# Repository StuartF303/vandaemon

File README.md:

# VanDaemon - Camper Van Control System

A comprehensive IoT control system for camper vans built with .NET 10 and Blazor WebAssembly. Monitor and control your van's systems including water tanks, LPG, lighting, heating, and more - all from your phone, tablet, or computer.

## Features

- **Real-time Monitoring**: Track water tanks, waste water, LPG, fuel, and battery levels in real-time
- **Interactive Controls**: Control lights, water pump, heater, and other systems with a touch-friendly interface
- **Configurable Alerts**: Get notified when tanks are running low or waste tanks are full
- **Multiple Van Types**: Support for different van models with customizable diagrams (default: Mercedes Sprinter LWB)
- **Modular Plugin System**: Easy integration with various hardware systems (Modbus, I2C, Victron Cerbo, etc.)
- **Web-Based Interface**: Access from any device with a web browser
- **Containerized Deployment**: Easy deployment with Docker on Raspberry Pi or other Linux systems
- **Offline-First**: Works without internet connectivity

## Quick Start

### Prerequisites

- [.NET 10.0 SDK](https://dotnet.microsoft.com/download/dotnet/10.0) (for development)
- [Docker](https://docs.docker.com/get-docker/) (for containerized deployment)
- Raspberry Pi 4 (2GB+ RAM recommended) or similar Linux system

### Running with Docker (Recommended)

1. Clone the repository:
```bash
git clone https://github.com/yourusername/vandaemon.git
cd vandaemon
```

2. Start the services:
```bash
docker compose up -d
```

For detailed Docker usage, configuration, and troubleshooting, see [DOCKER.md](DOCKER.md).

3. Access the web interface:
- Web UI: http://localhost:8080
- API: http://localhost:5000
- API Documentation: http://localhost:5000/swagger

### Running for Development

1. Build the solution:
```bash
./build.sh          # Linux/Mac
build.bat           # Windows
```

2. Run the API:
```bash
cd src/Backend/VanDaemon.Api
dotnet run
```

3. Run the Web UI (in a separate terminal):
```bash
cd src/Frontend/VanDaemon.Web
dotnet run
```

## Project Structure

```
VanDaemon/
├── src/
│   ├── Backend/
│   │   ├── VanDaemon.Api/              # REST API and SignalR hubs
│   │   ├── VanDaemon.Core/             # Domain models and interfaces
│   │   ├── VanDaemon.Application/      # Business logic services
│   │   ├── VanDaemon.Infrastructure/   # Data access and external services
│   │   └── VanDaemon.Plugins/          # Hardware integration plugins
│   │       ├── Abstractions/           # Plugin interfaces
│   │       ├── Simulated/              # Simulated hardware (for testing)
│   │       ├── Modbus/                 # Modbus integration
│   │       ├── I2C/                    # I2C sensor integration
│   │       └── Victron/                # Victron Cerbo integration
│   └── Frontend/
│       └── VanDaemon.Web/              # Blazor WebAssembly application
├── tests/                              # Unit and integration tests
├── docs/                               # Documentation
├── docker/                             # Docker configuration
└── .github/workflows/                  # CI/CD pipelines
```

## Architecture

VanDaemon follows a clean architecture pattern with clear separation of concerns:

- **Frontend**: Blazor WebAssembly with MudBlazor UI components
- **Backend API**: ASP.NET Core Web API with SignalR for real-time updates
- **Plugin System**: Modular hardware integration layer supporting multiple protocols
- **Data Storage**: JSON file storage for configuration, in-memory cache for real-time data

See [PROJECT_PLAN.md](PROJECT_PLAN.md) for detailed architecture documentation.

## Hardware Integration

VanDaemon supports multiple hardware integration methods through its plugin system:

### Supported Plugins

1. **Simulated Plugin** (Default) - For testing and development
2. **MqttLedDimmer Plugin** - VANDIMMER-4CH+2A LED dimmer boards over MQTT. Auto-discovers
   devices from their retained `config` message and registers each channel as a Dimmer
   control. Working against real hardware as of 2026-09-10; see
   [hw/VDDimmer/firmware/README.md](hw/VDDimmer/firmware/README.md) for the topic contract.
3. **Modbus Plugin** - For Modbus TCP/RTU devices
4. **I2C Plugin** - For direct I2C sensor integration
5. **Victron Plugin** - For Victron Cerbo GX integration via MQTT

Driving real hardware needs an MQTT broker the API can reach; `MqttLedDimmer:MqttBroker` in
`appsettings.json` defaults to `localhost:1883`.

### Adding a New Plugin

See [docs/deployment/plugin-development.md](docs/deployment/plugin-development.md) for instructions on creating custom hardware plugins.

## Configuration

### System Settings

Configure the system through the web interface Settings page or by editing the configuration files:

- `appsettings.json` - API configuration
- Environment variables - Runtime configuration

### Van Diagram Configuration

Customize the van diagram to match your vehicle:

1. Create an SVG diagram of your van (facing left)
2. Add the diagram to `src/Frontend/VanDaemon.Web/wwwroot/diagrams/`
3. Configure overlay positions in the Settings page

## Deployment

VanDaemon supports multiple deployment options:

### Cloud Deployment (Fly.io)

Deploy VanDaemon to the cloud for remote access as a single combined container:

```bash
# Install Fly.io CLI
curl -L https://fly.io/install.sh | sh

# Login and deploy
flyctl auth login
flyctl apps create vandaemon
flyctl deploy
```

Access your application at:
- **Single URL**: https://vandaemon.fly.dev
  - Web Frontend: `/`
  - API Backend: `/api`
  - SignalR WebSocket: `/hubs`
  - Health Check: `/health`

#### Architecture
The Fly.io deployment uses a single container with:
- **Nginx** (Port 8080) - Serves Blazor WASM static files and proxies API/WebSocket requests
- **.NET API** (Port 5000 internal) - Handles REST API and SignalR connections
- **Supervisor** - Manages both nginx and API processes

#### Key Features
- **Single Endpoint**: All services accessible from one URL
- **WebSocket Support**: Nginx configured for long-lived SignalR connections
- **Health Checks**: Automatic monitoring via `/health` endpoint
- **Auto-Scaling**: Machines stop when idle to save costs
- **GitHub Actions**: Automatic deployment on push to main branch

For detailed instructions including GitHub Actions auto-deployment, see **[DEPLOYMENT.md](DEPLOYMENT.md)**

### Local/Raspberry Pi Deployment

### Step 1: Prepare the Raspberry Pi

```bash
# Update system
sudo apt update && sudo apt upgrade -y

# Install Docker (includes Docker Compose V2)
curl -fsSL https://get.docker.com -o get-docker.sh
sudo sh get-docker.sh

# Add user to docker group
sudo usermod -aG docker $USER
```

### Step 2: Clone and Deploy

```bash
git clone https://github.com/yourusername/vandaemon.git
cd vandaemon
docker compose up -d
```

### Step 3: Configure Hardware Access

For GPIO/I2C access, you may need to:

```bash
# Enable I2C
sudo raspi-config
# Select: Interface Options -> I2C -> Enable

# Add user to i2c group
sudo usermod -aG i2c $USER
```

### Step 4: Set Up Auto-Start

```bash
# Create systemd service
sudo nano /etc/systemd/system/vandaemon.service
```

Add the following content:
```ini
[Unit]
Description=VanDaemon Control System
Requires=docker.service
After=docker.service

[Service]
Type=oneshot
RemainAfterExit=yes
WorkingDirectory=/home/pi/vandaemon
ExecStart=/usr/bin/docker compose up -d
ExecStop=/usr/bin/docker compose down

[Install]
WantedBy=multi-user.target
```

Enable and start:
```bash
sudo systemctl enable vandaemon
sudo systemctl start vandaemon
```

## API Documentation

The API is documented with OpenAPI/Swagger. Access the interactive documentation at:
- http://localhost:5000/swagger (when running locally)
- https://vandaemon.fly.dev/swagger (when deployed)

### Key Endpoints

- `GET /api/tanks` - Get all tanks
- `GET /api/tanks/{id}/level` - Get current tank level
- `POST /api/tanks/refresh` - Refresh all tank levels
- `PUT /api/tanks/{id}` - Update tank configuration
- `GET /health` - Health check endpoint (returns status and timestamp)

### Real-Time Updates

SignalR hub for real-time telemetry updates:
- **Local**: ws://localhost:5000/hubs/telemetry
- **Cloud**: wss://vandaemon.fly.dev/hubs/telemetry

The hub broadcasts tank levels, control states, and alerts to all connected clients.

## Development

### Building from Source

```bash
# Build solution
dotnet build VanDaemon.sln

# Run tests
dotnet test VanDaemon.sln

# Run specific project
cd src/Backend/VanDaemon.Api
dotnet run
```

### Running Tests

```bash
# Run all tests
dotnet test

# Run with coverage
dotnet test --collect:"XPlat Code Coverage"
```

## Roadmap

See [PROJECT_PLAN.md](PROJECT_PLAN.md) for the detailed development roadmap.

## Troubleshooting

### Common Issues

**Issue**: Cannot connect to API from web interface
- Check that API is running on http://localhost:5000
- Verify CORS settings in `appsettings.json`
- Check browser console for errors
- The frontend automatically uses the current host URL (no configuration needed)

**Issue**: Docker containers won't start
- Run `docker compose logs` to check logs
- Ensure ports 5000 and 8080 are not in use
- Verify Docker daemon is running

**Issue**: Sensors not reading values
- Check plugin configuration in Settings
- Verify hardware connections
- Check API logs for errors

**Issue**: SignalR WebSocket connections failing
- Verify health endpoint is accessible: `curl https://your-app.fly.dev/health`
- Check nginx logs for WebSocket upgrade errors
- Ensure nginx is configured with proper WebSocket headers
- Check for firewall blocking WebSocket connections (port 443 for wss://)

**Issue**: Fly.io deployment health checks failing
- Verify the `/health` endpoint returns 200 OK
- Check logs: `flyctl logs --app vandaemon`
- Ensure nginx and API are both running: `flyctl ssh console -C "supervisorctl status"`

**Issue**: Frontend making requests to localhost in production
- This is now fixed automatically - the frontend uses `builder.HostEnvironment.BaseAddress`
- In production, it will use the deployed URL (e.g., https://vandaemon.fly.dev)
- In development, it will use http://localhost:8080

## License

This project is licensed under the MIT License - see the [LICENSE](LICENSE) file for details.

## Acknowledgments

- [MudBlazor](https://mudblazor.com/) - Material Design components for Blazor
- [NModbus](https://github.com/NModbus/NModbus) - Modbus communication library
- [Victron Energy](https://www.victronenergy.com/) - For their excellent products and documentation

---

Built with ❤️ for the camper van community

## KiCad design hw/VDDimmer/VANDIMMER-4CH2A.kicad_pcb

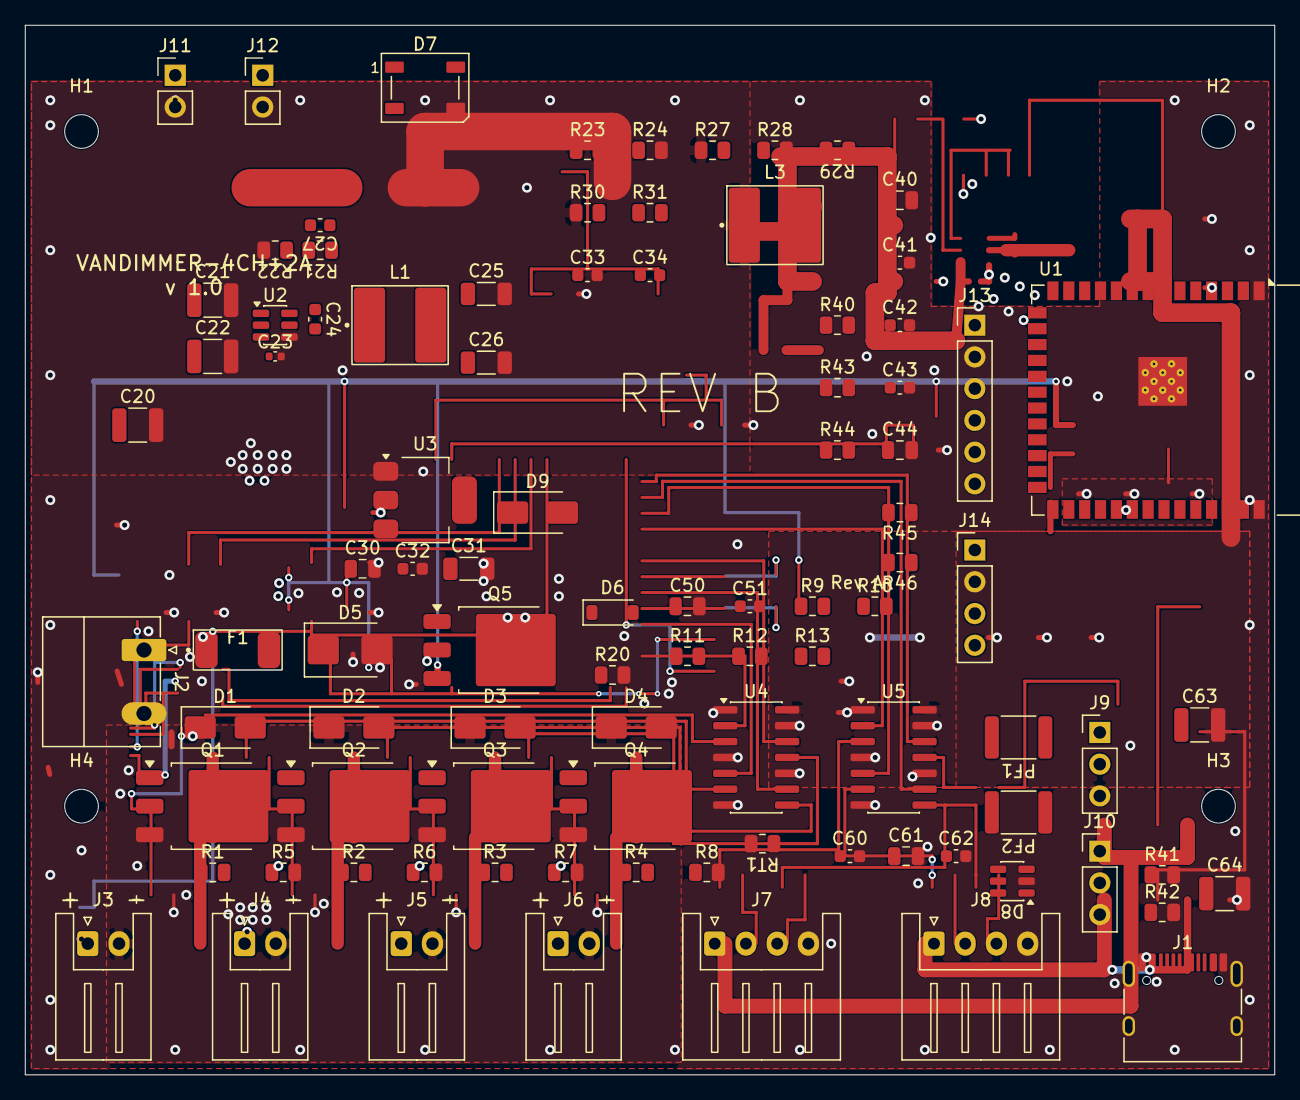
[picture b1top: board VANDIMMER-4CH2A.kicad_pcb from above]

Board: 4 copper layers, 100.0 x 84.0 mm, 98 parts (0 on the bottom side), 61 nets.

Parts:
C20, C63, C64: 10uF/50V; C_1210_3225Metric
C21, C22: 10uF/50V X7R; C_1210_3225Metric
C23: 100nF/25V; C_0402_1005Metric
C24, C32, C33, C34, C41, C42, C43, C51, C60, C62: 100nF/50V; C_0603_1608Metric
C25, C26, C31: 22uF/25V; C_1206_3216Metric
C27: 22pF; C_0603_1608Metric
C30, C40, C44, C50, C61: 10uF/25V; C_0805_2012Metric
D1, D2, D3, D4, D9: SS34; D_SMA
D5: SMBJ18A; D_SMB
D6: BZT52C12; D_SOD-123
D7: WS2812B-V6; LED_WS2812B_PLCC4_5.0x5.0mm_P3.2mm
D8: USBLC6-2SC6; SOT-23-6
F1: 8A 250V; Fuse_2410_6125Metric
H1, H2, H3, H4: M2.5; MountingHole_2.7mm_M2.5
J1: USB-C 16P; USB_C_Receptacle_HRO_TYPE-C-31-M-12
J2: VIN 12V; PhoenixContact_MC_1,5_2-G-5.08_1x02_P5.08mm_Horizontal
J3: CH1 LED-/V+; JST_XH_S2B-XH-A_1x02_P2.50mm_Horizontal
J4: CH2 LED-/V+; JST_XH_S2B-XH-A_1x02_P2.50mm_Horizontal
J5: CH3 LED-/V+; JST_XH_S2B-XH-A_1x02_P2.50mm_Horizontal
J6: CH4 LED-/V+; JST_XH_S2B-XH-A_1x02_P2.50mm_Horizontal
J7: ADDR1 V+/D/CLK/GND; JST_XH_S4B-XH-A_1x04_P2.50mm_Horizontal
J8: ADDR2 V+/D/CLK/GND; JST_XH_S4B-XH-A_1x04_P2.50mm_Horizontal
J9: A1 V+SEL VIN/5V; PinHeader_1x03_P2.54mm_Vertical
J10: A2 V+SEL VIN/5V; PinHeader_1x03_P2.54mm_Vertical
J11: BTN1; PinHeader_1x02_P2.54mm_Vertical
J12: BTN2; PinHeader_1x02_P2.54mm_Vertical
J13: EXP 3V3/GND/SDA/SCL/EN/IO0; PinHeader_1x06_P2.54mm_Vertical
J14: UART1 3V3/GND/TX/RX; PinHeader_1x04_P2.54mm_Vertical
L1: 10uH 4.5A; L_cjiang_FXL0630_7.0x6.6mm
L3: 10uH; L_cjiang_FXL0630_7.0x6.6mm
PF1, PF2: PTC 3A 30V; R_1812_4532Metric
Q1, Q2, Q3, Q4: 20N06; TO-252-3_TabPin2
Q5: SUD50P06-15; TO-252-3_TabPin2
R1, R2, R3, R4: 220R; R_0805_2012Metric
R5, R6, R7, R8, R40, R43, R44: 10k; R_0805_2012Metric
R9, R10, R11, R12, R13: 47R; R_0805_2012Metric
R20: 100k; R_0805_2012Metric
R21: 52.3k 1%; R_0805_2012Metric
R22, R28, R29: 10k 1%; R_0805_2012Metric
R23, R27: 100k 1%; R_0805_2012Metric
R24: 18k 1%; R_0805_2012Metric
R30: 0R; R_0805_2012Metric
R31: 1R; R_0805_2012Metric
R41, R42: 5.1k; R_0805_2012Metric
R45, R46: 4.7k; R_0805_2012Metric
RT1: NTC 10k B3950; R_0805_2012Metric
U1: ESP32-S3-WROOM-1-N16R8; ESP32-S3-WROOM-1
U2: AP63301WU-7; TSOT-23-6
U3: BL1117-33CX; SOT-223-3_TabPin2
U4, U5: 74HCT125; SOIC-14_3.9x8.7mm_P1.27mm

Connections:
+3V3: C31.1, C32.1, C40.1, C41.1, C42.1, J13.1, J14.1, R29.1, R40.1, R43.1, R44.1, R45.1, R46.1, U1.2 (3V3), U3.2 (VO)
+5V: C25.1, C26.1, C27.1, C30.1, C50.1, C51.1, C60.1, C61.1, C62.1, D7.1 (VDD), D9.1 (K), J9.3, J10.3, L1.2, R21.1, U3.3 (VI), U4.14 (VCC), U5.14 (VCC)
/Addressable/ADDR1_CLK: J7.3, R11.2
/Addressable/ADDR1_D5V: R9.1, U5.3
/Addressable/ADDR1_DATA: J7.2, R9.2
/Addressable/ADDR1_VOUT: C63.1, J7.1, PF1.2
/Addressable/ADDR1_VSEL: J9.2, PF1.1
/Addressable/ADDR2_CLK: J8.3, R12.2
/Addressable/ADDR2_D5V: R10.1, U5.6
/Addressable/ADDR2_DATA: J8.2, R10.2
/Addressable/ADDR2_VOUT: C64.1, J8.1, PF2.2
/Addressable/ADDR2_VSEL: J10.2, PF2.1
/Addressable/ADDR_CLK5V: R11.1, R12.1, U5.8
/Addressable/STATUS_D: D7.4 (DIN), R13.2
/Addressable/STATUS_D5V: R13.1, U5.11
/MCU/BOOT_IO0: J13.6, U1.27 (IO0)
/MCU/BTN1: J11.1, R43.2, U1.33 (IO40)
/MCU/BTN2: J12.1, R44.2, U1.32 (IO39)
/MCU/EN_MCU: C43.1, J13.5, R40.2, U1.3 (EN)
/MCU/I2C_SCL: J13.4, R46.2, U1.18 (IO10)
/MCU/I2C_SDA: J13.3, R45.2, U1.20 (IO12)
/MCU/UART1_RX: J14.4, U1.34 (IO41)
/MCU/UART1_TX: J14.3, U1.35 (IO42)
/MCU/USB_CC1: J1.A5 (CC1), R41.1
/MCU/USB_CC2: J1.B5 (CC2), R42.1
/MCU/USB_DM: D8.3 (I/O2), D8.4 (I/O2), J1.A7 (D-), J1.B7 (D-), U1.13 (USB_D-)
/MCU/USB_DP: D8.1 (I/O1), D8.6 (I/O1), J1.A6 (D+), J1.B6 (D+), U1.14 (USB_D+)
/MCU/VBUS: C44.1, D8.5 (VBUS), D9.2 (A), J1.A4 (VBUS), J1.A9 (VBUS), J1.B4 (VBUS), J1.B9 (VBUS)
/PWM/DRAIN1: D1.2 (A), J3.1, Q1.2 (D)
/PWM/DRAIN2: D2.2 (A), J4.1, Q2.2 (D)
/PWM/DRAIN3: D3.2 (A), J5.1, Q3.2 (D)
/PWM/DRAIN4: D4.2 (A), J6.1, Q4.2 (D)
/PWM/GATE1: Q1.1 (G), R1.2, R5.1
/PWM/GATE2: Q2.1 (G), R2.2, R6.1
/PWM/GATE3: Q3.1 (G), R3.2, R7.1
/PWM/GATE4: Q4.1 (G), R4.2, R8.1
/PWM/GDRV1: R1.1, U4.3
/PWM/GDRV2: R2.1, U4.6
/PWM/GDRV3: R3.1, U4.8
/PWM/GDRV4: R4.1, U4.11
/Power/BST: C24.1, U2.6 (BST)
/Power/EN_BUCK: R23.2, R24.1, U2.2 (EN)
/Power/FB: C27.2, R21.2, R22.1, U2.1 (FB)
/Power/QREV_G: D6.2 (A), Q5.1 (G), R20.1
/Power/SW: C24.2, L1.1, U2.5 (SW)
/Power/VIN_BUCK: C21.1, C22.1, C23.1, L3.2, R23.1, R30.2, R31.1, U2.3 (VIN)
/Power/VIN_DAMP: C20.1, R31.2
/Power/VIN_FUSED: D5.1 (A1), F1.2, Q5.2 (D)
/Power/VIN_RAW: F1.1, J2.1
ADDR1_DIN: U1.23 (IO21), U5.2
ADDR2_DIN: U1.24 (IO47), U5.5
ADDR_CLK: U1.25 (IO48), U5.9
GATE_IN1: U1.15 (IO3), U4.2
GATE_IN2: U1.17 (IO9), U4.5
GATE_IN3: U1.19 (IO11), U4.9
GATE_IN4: U1.21 (IO13), U4.12
GND: C20.2, C21.2, C22.2, C23.2, C25.2, C26.2, C30.2, C31.2, C32.2, C33.2, C34.2, C40.2, C41.2, C42.2, C43.2, C44.2, C50.2, C51.2, C60.2, C61.2, C62.2, C63.2, C64.2, D5.2 (A2), D7.3 (VSS), D8.2 (GND), J1.A1 (GND), J1.A12 (GND), J1.B1 (GND), J1.B12 (GND), J1.SH (SHIELD), J2.2, J7.4, J8.4, J11.2, J12.2, J13.2, J14.2, Q1.3 (S), Q2.3 (S), Q3.3 (S), Q4.3 (S), R5.2, R6.2, R7.2, R8.2, R20.2, R22.2, R24.2, R28.2, R41.2, R42.2, RT1.2, U1.1 (GND), U1.40 (GND), U1.41 (GND), U2.4 (GND), U3.1 (GND), U4.1, U4.4, U4.7 (GND), U4.10, U4.13, U5.1, U5.4, U5.7 (GND), U5.10, U5.13
NTC_SENSE: C34.1, R29.2, RT1.1, U1.38 (IO2)
STATUS_DIN: U1.26 (IO45), U5.12
VIN_PROT: D1.1 (K), D2.1 (K), D3.1 (K), D4.1 (K), D6.1 (K), J3.2, J4.2, J5.2, J6.2, J9.1, J10.1, L3.1, Q5.3 (S), R27.1, R30.1
VIN_SENSE: C33.1, R27.2, R28.1, U1.39 (IO1)

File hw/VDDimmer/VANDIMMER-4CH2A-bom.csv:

"Reference","Value","Footprint","MPN","LCSC","Manufacturer","QUANTITY","DNP"
"C20,C63,C64","10uF/50V","Capacitor_SMD:C_1210_3225Metric","HGC1210R7106M500NSVK","C33546018","Chinocera","3",""
"C21,C22","10uF/50V X7R","Capacitor_SMD:C_1210_3225Metric","HGC1210R7106M500NSVK","C33546018","Chinocera","2",""
"C23","100nF/25V","Capacitor_SMD:C_0402_1005Metric","CL05B104KB54PNC","C307331","Samsung Electro-Mechanics","1",""
"C24,C32-C34,C41-C43,C51,C60,C62","100nF/50V","Capacitor_SMD:C_0603_1608Metric","CC0603KRX7R9BB104","C14663","YAGEO","10",""
"C25,C26,C31","22uF/25V","Capacitor_SMD:C_1206_3216Metric","CL31A226KAHNNNE","C12891","Samsung Electro-Mechanics","3",""
"C27","22pF","Capacitor_SMD:C_0603_1608Metric","CL10C220JB8NNNC","C1653","Samsung Electro-Mechanics","1",""
"C30,C40,C44,C50,C61","10uF/25V","Capacitor_SMD:C_0805_2012Metric","CL21A106KAYNNNE","C15850","Samsung Electro-Mechanics","5",""
"D1-D4,D9","SS34","Diode_SMD:D_SMA","SS34","C8678","MDD","5",""
"D5","SMBJ18A","Diode_SMD:D_SMB","SMBJ18A","C19077573","hongjiacheng","1",""
"D6","BZT52C12","Diode_SMD:D_SOD-123","BZT52C12","C19077410","hongjiacheng","1",""
"D7","WS2812B-V6","LED_SMD:LED_WS2812B_PLCC4_5.0x5.0mm_P3.2mm","WS2812B-V5/W","C2874885","Worldsemi","1",""
"D8","USBLC6-2SC6","Package_TO_SOT_SMD:SOT-23-6","USBLC6-2SC6","C2687116","UMW","1",""
"F1","8A 250V","VANDIMMER:Fuse_2410_6125Metric","LTC2410-1800TSK","C54824501","LUTE","1",""
"H1-H4","M3","MountingHole:MountingHole_3.2mm_M3","","","","4",""
"J1","USB-C 16P","Connector_USB:USB_C_Receptacle_HRO_TYPE-C-31-M-12","TYPE-C-31-M-12","C165948","Korean Hroparts Elec","1",""
"J2","VIN 12V","Connector_Phoenix_MC_HighVoltage:PhoenixContact_MC_1,5_2-G-5.08_1x02_P5.08mm_Horizontal","MC 1,5/2-G-5.08","","Phoenix Contact","1",""
"J3","CH1 V+/LED-","Connector_JST:JST_XH_S2B-XH-A_1x02_P2.50mm_Horizontal","","","","1",""
"J4","CH2 V+/LED-","Connector_JST:JST_XH_S2B-XH-A_1x02_P2.50mm_Horizontal","","","","1",""
"J5","CH3 V+/LED-","Connector_JST:JST_XH_S2B-XH-A_1x02_P2.50mm_Horizontal","","","","1",""
"J6","CH4 V+/LED-","Connector_JST:JST_XH_S2B-XH-A_1x02_P2.50mm_Horizontal","","","","1",""
"J7","ADDR1 V+/D/CLK/GND","Connector_JST:JST_XH_S4B-XH-A_1x04_P2.50mm_Horizontal","","","","1",""
"J8","ADDR2 V+/D/CLK/GND","Connector_JST:JST_XH_S4B-XH-A_1x04_P2.50mm_Horizontal","","","","1",""
"J9","A1 V+SEL VIN/5V","Connector_PinHeader_2.54mm:PinHeader_1x03_P2.54mm_Vertical","","","","1",""
"J10","A2 V+SEL VIN/5V","Connector_PinHeader_2.54mm:PinHeader_1x03_P2.54mm_Vertical","","","","1",""
"J11","BTN1","Connector_PinHeader_2.54mm:PinHeader_1x02_P2.54mm_Vertical","","","","1",""
"J12","BTN2","Connector_PinHeader_2.54mm:PinHeader_1x02_P2.54mm_Vertical","","","","1",""
"J13","EXP 3V3/GND/SDA/SCL/EN/IO0","Connector_PinHeader_2.54mm:PinHeader_1x06_P2.54mm_Vertical","","","","1",""
"J14","UART1 3V3/GND/TX/RX","Connector_PinHeader_2.54mm:PinHeader_1x04_P2.54mm_Vertical","","","","1",""
"L1","10uH 4.5A","VANDIMMER:L_cjiang_FXL0630_7.0x6.6mm","PNLS6045-100M","C2849537","DMBJ","1",""
"L3","10uH","VANDIMMER:L_cjiang_FXL0630_7.0x6.6mm","PNLS6045-100M","C2849537","DMBJ","1",""
"PF1,PF2","PTC 2A 30V","Resistor_SMD:R_1812_4532Metric","1812L200/30GR","C18198342","LUTE","2",""
"Q1-Q4","20N06","Package_TO_SOT_SMD:TO-252-3_TabPin2","20N06","C2890395","UMW","4",""
"Q5","SUD50P06-15","Package_TO_SOT_SMD:TO-252-3_TabPin2","SUD50P06-15(UMW)","C7503186","UMW","1",""
"R1-R4","220R","Resistor_SMD:R_0805_2012Metric","0805W8F2200T5E","C17557","UNI-ROYAL","4",""
"R5-R8,R40,R43,R44","10k","Resistor_SMD:R_0805_2012Metric","0805W8F1002T5E","C17414","UNI-ROYAL","7",""
"R9,R10,R13","47R","Resistor_SMD:R_0805_2012Metric","0805W8F470JT5E","C17714","UNI-ROYAL","3",""
"R11,R12","47R","Resistor_SMD:R_0805_2012Metric","0805W8F470JT5E","C17714","UNI-ROYAL","2","DNP"
"R20","100k","Resistor_SMD:R_0805_2012Metric","0805W8F1003T5E","C149504","UNI-ROYAL","1",""
"R21","52.3k 1%","Resistor_SMD:R_0805_2012Metric","FRC0805F5232TS","C2933465","FOJAN","1",""
"R22,R28,R29","10k 1%","Resistor_SMD:R_0805_2012Metric","0805W8F1002T5E","C17414","UNI-ROYAL","3",""
"R23,R27","100k 1%","Resistor_SMD:R_0805_2012Metric","0805W8F1003T5E","C149504","UNI-ROYAL","2",""
"R24","18k 1%","Resistor_SMD:R_0805_2012Metric","0805W8F1802T5E","C17506","UNI-ROYAL","1",""
"R30","0R","Resistor_SMD:R_0805_2012Metric","0805W8F0000T5E","C17477","UNI-ROYAL","1","DNP"
"R31","1R","Resistor_SMD:R_0805_2012Metric","0805W8F100KT5E","C25271","UNI-ROYAL","1",""
"R41,R42","5.1k","Resistor_SMD:R_0805_2012Metric","0805W8F5101T5E","C27834","UNI-ROYAL","2",""
"R45,R46","4.7k","Resistor_SMD:R_0805_2012Metric","0805W8F4701T5E","C17673","UNI-ROYAL","2",""
"RT1","NTC 10k B3950","Resistor_SMD:R_0805_2012Metric","HNTC0805-103F3950FB","C49247662","hongjiacheng","1",""
"U1","ESP32-S3-WROOM-1U-N16","RF_Module:ESP32-S3-WROOM-1U","ESP32-S3-WROOM-1U-N16","C2980298","Espressif Systems","1",""
"U2","AP63301WU-7","Package_TO_SOT_SMD:TSOT-23-6","AP63301WU-7","C2158003","Diodes Incorporated","1",""
"U3","BL1117-33CX","Package_TO_SOT_SMD:SOT-223-3_TabPin2","BL1117-33CX","C5400","BL (Shanghai Belling)","1",""
"U4,U5","74HCT125","Package_SO:SOIC-14_3.9x8.7mm_P1.27mm","74HCT125D,653","C5962","Nexperia","2",""

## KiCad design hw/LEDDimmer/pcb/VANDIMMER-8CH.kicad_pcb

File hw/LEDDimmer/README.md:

# MQTT LED Dimmer - VanDaemon Integration

## Overview

The MQTT LED Dimmer is an ESP32-based 8-channel PWM LED controller that integrates with the VanDaemon control system via MQTT. It supports multiple devices on the network, automatic discovery, and real-time state synchronization.

## Features

- **8-Channel PWM Control**: Individual brightness control (0-255) for each channel
- **MQTT Communication**: Bidirectional control and state reporting
- **WiFi Configuration**: Captive portal setup via WiFiManager
- **Auto-Discovery**: Automatic device registration in VanDaemon
- **State Persistence**: NVS storage for channel states across reboots
- **Status LED**: WS2812 RGB LED for visual device status feedback
- **OTA Updates**: Over-the-air firmware updates support
- **Multi-Device Support**: Multiple LED dimmers on the same network

## Hardware

### Supported Variants

- **4-Channel**: 4 PWM outputs (reduced version)
- **8-Channel**: Full 8 PWM outputs (default)

### Pin Configuration (ESP32)

```cpp
// PWM Outputs (8 channels)
GPIO 25, 26, 27, 14, 4, 5, 18, 19

// Status LED (WS2812)
GPIO 16

// Buttons
GPIO 32 (Button 1) - Fade demo
GPIO 33 (Button 2) - Toggle all channels
Hold both 3+ seconds - Reset WiFi
```

### Schematic

See `hw/LEDDimmer/schematic/` for complete circuit diagrams.

## Firmware

### Building and Uploading

```bash
cd hw/LEDDimmer/firmware

# Build for 8-channel variant (default)
pio run -e 8ch

# Upload via USB
pio run -e 8ch -t upload

# Build for 4-channel variant
pio run -e 4ch -t upload

# Build with OTA support
pio run -e 8ch-ota -t upload
```

### WiFi Configuration

1. Power on the device
2. Look for WiFi network: `VanDaemon-LED-XXXX`
3. Connect with password: `vandaemon`
4. Configure your WiFi credentials in the captive portal
5. Device will auto-connect and appear in VanDaemon

### MQTT Topic Structure

The device communicates using the following MQTT topic hierarchy:

**Base Topic**: `vandaemon/leddimmer/`

#### Device Topics

| Topic | Direction | Description | Payload |
|-------|-----------|-------------|---------|
| `{base}/{deviceId}/status` | Publish | Device online/offline status | `online` or `offline` |
| `{base}/{deviceId}/config` | Publish | Device configuration | JSON object |
| `{base}/{deviceId}/heartbeat` | Publish | Periodic heartbeat | JSON object |

#### Channel Topics

| Topic | Direction | Description | Payload |
|-------|-----------|-------------|---------|
| `{base}/{deviceId}/channel/{N}/state` | Publish | Current brightness (0-255) | Integer |
| `{base}/{deviceId}/channel/{N}/set` | Subscribe | Set brightness command | Integer or JSON |

**Example deviceId**: `cabin-lights`, `galley-leds`, `bedroom-dimmer`

### Configuration Message

Published to `vandaemon/leddimmer/{deviceId}/config` on startup:

```json
{
  "deviceId": "cabin-lights",
  "deviceName": "Cabin LED Dimmer",
  "channels": 8,
  "version": "1.0.0",
  "variant": "8CH"
}
```

### Heartbeat Message

Published to `vandaemon/leddimmer/{deviceId}/heartbeat` every 60 seconds:

```json
{
  "uptime": 3600,
  "freeHeap": 245000,
  "rssi": -65
}
```

### Control Commands

**Set Channel Brightness** (Integer format):
```
Topic: vandaemon/leddimmer/cabin-lights/channel/0/set
Payload: 128
```

**Set Channel Brightness** (JSON format):
```
Topic: vandaemon/leddimmer/cabin-lights/channel/0/set
Payload: {"brightness": 128}
```

## VanDaemon Backend Integration

### Architecture

The integration consists of two main components:

1. **MqttLedDimmerPlugin** (`src/Backend/VanDaemon.Plugins/VanDaemon.Plugins.MqttLedDimmer/MqttLedDimmerPlugin.cs`)
   - Implements `IControlPlugin` interface
   - Manages MQTT connection to broker
   - Handles device discovery via MQTT messages
   - Processes control commands and state updates

2. **MqttLedDimmerService** (`src/Backend/VanDaemon.Plugins/VanDaemon.Plugins.MqttLedDimmer/MqttLedDimmerService.cs`)
   - Background service that runs continuously
   - Discovers new devices every 10 seconds
   - Refreshes control states every 5 seconds
   - Automatically registers Control entities in VanDaemon

### Configuration

Edit `src/Backend/VanDaemon.Api/appsettings.json`:

```json
{
  "MqttLedDimmer": {
    "MqttBroker": "localhost",
    "MqttPort": 1883,
    "MqttUsername": "",
    "MqttPassword": "",
    "BaseTopic": "vandaemon/leddimmer",
    "AutoDiscovery": true,
    "Devices": []
  }
}
```

**Configuration Options**:

- `MqttBroker`: MQTT broker hostname or IP (default: `localhost`)
- `MqttPort`: MQTT broker port (default: `1883`)
- `MqttUsername`: MQTT authentication username (optional)
- `MqttPassword`: MQTT authentication password (optional)
- `BaseTopic`: Base MQTT topic prefix (default: `vandaemon/leddimmer`)
- `AutoDiscovery`: Enable automatic device discovery (default: `true`)
- `Devices`: Pre-configured device list (empty for auto-discovery)

### Control Entity Registration

When a device is discovered, the service automatically creates Control entities:

- **Type**: `ControlType.Dimmer`
- **Name**: `{DeviceName} - Channel {N}`
- **State**: Current brightness (0-255)
- **Icon**: `mdi-lightbulb-outline`
- **Plugin**: `MqttLedDimmer`
- **ControlId**: `{deviceId}-CH{N}` (e.g., `cabin-lights-CH0`)

### Docker Deployment

The MQTT broker is included in the Docker Compose setup:

```yaml
# docker-compose.yml (repo root — single authoritative stack)
mqtt:
  image: eclipse-mosquitto:2.0
  ports:
    - "1883:1883"      # MQTT
    - "9001:9001"      # WebSocket
  volumes:
    - ./mosquitto/config:/mosquitto/config
    - mqtt-data:/mosquitto/data
```

Start services (from the repo root):
```bash
docker compose up -d
```

## Status LED Indicators

The WS2812 RGB LED provides visual feedback:

| Color | Status |
|-------|--------|
| Blue (slow pulse) | WiFi connecting |
| Cyan (slow pulse) | MQTT connecting |
| Green (solid) | Connected and operational |
| Red (fast blink) | Error state |
| Yellow (solid) | Configuration mode |

## Button Functions

- **Button 1 (GPIO 32)**:
  - Short press: Run fade demo on all channels

- **Button 2 (GPIO 33)**:
  - Short press: Toggle all channels on/off

- **Both buttons (3+ seconds)**:
  - Reset WiFi credentials and restart in AP mode

## Troubleshooting

### Device Not Appearing in VanDaemon

1. **Check MQTT broker is running**:
   ```bash
   docker ps | grep mqtt
   ```

2. **Check device WiFi connection**:
   - Verify status LED is green
   - Check router/access point for device IP

3. **Check MQTT messages**:
   ```bash
   # Subscribe to all LED dimmer topics
   mosquitto_sub -h localhost -t "vandaemon/leddimmer/#" -v
   ```

4. **Check VanDaemon logs**:
   ```bash
   docker logs vandaemon-api
   ```
   Look for "Device discovered" or "MQTT connection" messages

### Channel Not Responding

1. **Check control state in VanDaemon dashboard**
2. **Publish test command**:
   ```bash
   mosquitto_pub -h localhost -t "vandaemon/leddimmer/cabin-lights/channel/0/set" -m "255"
   ```

3. **Check device serial monitor** (if connected via USB):
   ```bash
   pio device monitor -e 8ch
   ```

### WiFi Connection Issues

1. **Reset WiFi credentials**:
   - Hold both buttons for 3+ seconds
   - Device will restart in AP mode

2. **Check WiFi signal strength**:
   - Heartbeat message includes RSSI value
   - Values below -80 dBm indicate weak signal

### MQTT Authentication

If your broker requires authentication:

1. Update firmware `config.h`:
   ```cpp
   #define MQTT_USERNAME   "your-username"
   #define MQTT_PASSWORD   "your-password"
   ```

2. Update VanDaemon `appsettings.json`:
   ```json
   "MqttUsername": "your-username",
   "MqttPassword": "your-password"
   ```

## Development

### Firmware Development

```bash
cd hw/LEDDimmer/firmware

# Monitor serial output
pio device monitor -e 8ch

# Clean build
pio run -e 8ch -t clean
pio run -e 8ch

# Upload filesystem (if needed)
pio run -e 8ch -t uploadfs
```

### Testing MQTT Communication

**Subscribe to all topics**:
```bash
mosquitto_sub -h localhost -t "vandaemon/leddimmer/#" -v
```

**Simulate device online**:
```bash
mosquitto_pub -h localhost -t "vandaemon/leddimmer/test-device/status" -m "online"
```

**Simulate config message**:
```bash
mosquitto_pub -h localhost -t "vandaemon/leddimmer/test-device/config" \
  -m '{"deviceId":"test-device","deviceName":"Test Dimmer","channels":8,"version":"1.0.0"}'
```

**Set channel brightness**:
```bash
mosquitto_pub -h localhost -t "vandaemon/leddimmer/test-device/channel/0/set" -m "128"
```

## Future Enhancements

- [ ] Web-based configuration interface
- [ ] Custom PWM frequency configuration
- [ ] Smooth transitions with configurable duration
- [ ] Scene/preset support
- [ ] Integration with VanDaemon automation rules
- [ ] MQTT TLS/SSL support
- [ ] HomeAssistant MQTT Discovery protocol support
- [ ] Current/power monitoring for channels

## License

Part of the VanDaemon project.

## Support

For issues and questions:
- Check logs: `docker logs vandaemon-api`
- MQTT monitoring: `mosquitto_sub -h localhost -t "vandaemon/leddimmer/#" -v`
- Serial monitor: `pio device monitor -e 8ch`

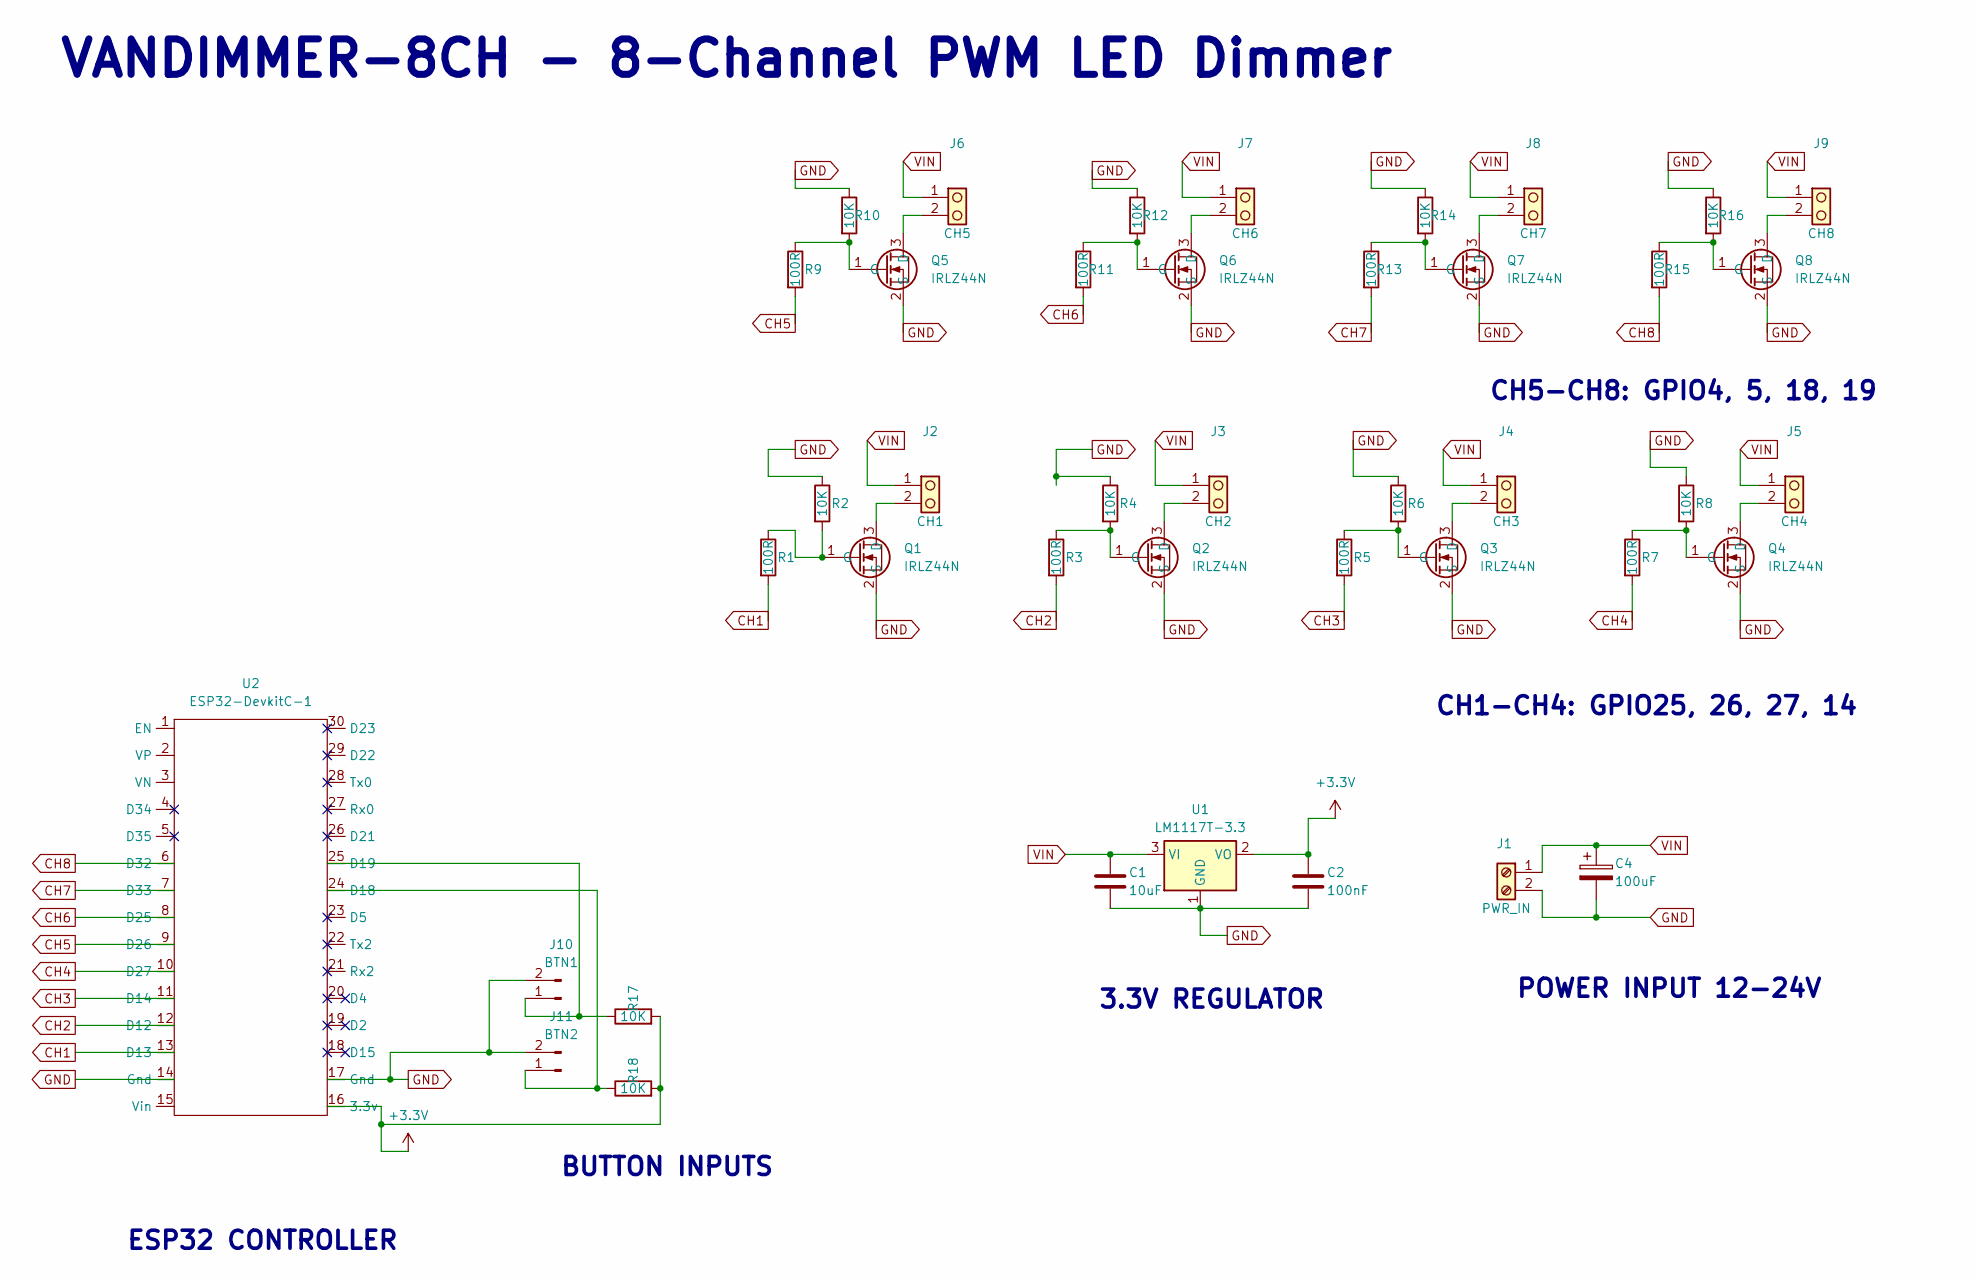
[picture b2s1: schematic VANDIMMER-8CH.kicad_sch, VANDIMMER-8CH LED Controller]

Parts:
C1: 10uF; C_Disc_D4.3mm_W1.9mm_P5.00mm
C2: 100nF; C_Disc_D4.3mm_W1.9mm_P5.00mm
C4: 100uF; CP_Radial_D8.0mm_P3.50mm
J1: PWR_IN; TerminalBlock_bornier-2_P5.08mm
J2: CH1; TerminalBlock_Xinya_XY308-2.54-2P_1x02_P2.54mm_Horizontal
J3: CH2; TerminalBlock_Xinya_XY308-2.54-2P_1x02_P2.54mm_Horizontal
J4: CH3; TerminalBlock_Xinya_XY308-2.54-2P_1x02_P2.54mm_Horizontal
J5: CH4; TerminalBlock_Xinya_XY308-2.54-2P_1x02_P2.54mm_Horizontal
J6: CH5; TerminalBlock_Xinya_XY308-2.54-2P_1x02_P2.54mm_Horizontal
J7: CH6; TerminalBlock_Xinya_XY308-2.54-2P_1x02_P2.54mm_Horizontal
J8: CH7; TerminalBlock_Xinya_XY308-2.54-2P_1x02_P2.54mm_Horizontal
J9: CH8; TerminalBlock_Xinya_XY308-2.54-2P_1x02_P2.54mm_Horizontal
J10: BTN1; PinHeader_1x02_P2.54mm_Vertical
J11: BTN2; PinHeader_1x02_P2.54mm_Vertical
Q1, Q2, Q3, Q4, Q5, Q6, Q7, Q8: IRLZ44N; TO-220-3_Horizontal_TabDown
R1, R3, R5, R7, R9, R11, R13, R15: 100R; R_Axial_DIN0207_L6.3mm_D2.5mm_P7.62mm_Horizontal
R2, R4, R6, R8, R10, R12, R14, R16, R17, R18: 10K; R_Axial_DIN0207_L6.3mm_D2.5mm_P7.62mm_Horizontal
U1: LM1117T-3.3; TO-220-3_Horizontal_TabDown
U2: ESP32-DevkitC-1; ESP32-DevKitC-1

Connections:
+3.3V: C2.1, R17.2, R18.2, U1.2 (VO), U2.16 (3.3v)
CH1: R1.2, U2.13 (D13)
CH2: R3.2, U2.12 (D12)
CH3: R5.2, U2.11 (D14)
CH4: R7.2, U2.10 (D27)
CH5: R9.2, U2.9 (D26)
CH6: R11.2, U2.8 (D25)
CH7: R13.2, U2.7 (D33)
CH8: R15.2, U2.6 (D32)
GND: C1.2, C2.2, C4.2, J1.2, J10.2, J11.2, Q1.2 (S), Q2.2 (S), Q3.2 (S), Q4.2 (S), Q5.2 (S), Q6.2 (S), Q7.2 (S), Q8.2 (S), R2.1, R4.1, R6.1, R8.1, R10.1, R12.1, R14.1, R16.1, U1.1 (GND), U2.14 (Gnd), U2.17 (Gnd)
unnamed: J2.2, Q1.3 (D)
unnamed: J3.2, Q2.3 (D)
unnamed: J4.2, Q3.3 (D)
unnamed: J5.2, Q4.3 (D)
unnamed: J6.2, Q5.3 (D)
unnamed: J7.2, Q6.3 (D)
unnamed: J8.2, Q7.3 (D)
unnamed: J9.2, Q8.3 (D)
unnamed: J10.1, R17.1, U2.25 (D19)
unnamed: J11.1, R18.1, U2.24 (D18)
unnamed: Q1.1 (G), R1.1, R2.2
unnamed: Q2.1 (G), R3.1, R4.2
unnamed: Q3.1 (G), R5.1, R6.2
unnamed: Q4.1 (G), R7.1, R8.2
unnamed: Q5.1 (G), R9.1, R10.2
unnamed: Q6.1 (G), R11.1, R12.2
unnamed: Q7.1 (G), R13.1, R14.2
unnamed: Q8.1 (G), R15.1, R16.2
VIN: C1.1, C4.1, J1.1, J2.1, J3.1, J4.1, J5.1, J6.1, J7.1, J8.1, J9.1, U1.3 (VI)

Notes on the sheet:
ESP32 CONTROLLER
VANDIMMER-8CH - 8-Channel PWM LED Dimmer
BUTTON INPUTS
CH5-CH8: GPIO4, 5, 18, 19
CH1-CH4: GPIO25, 26, 27, 14
POWER INPUT 12-24V
3.3V REGULATOR

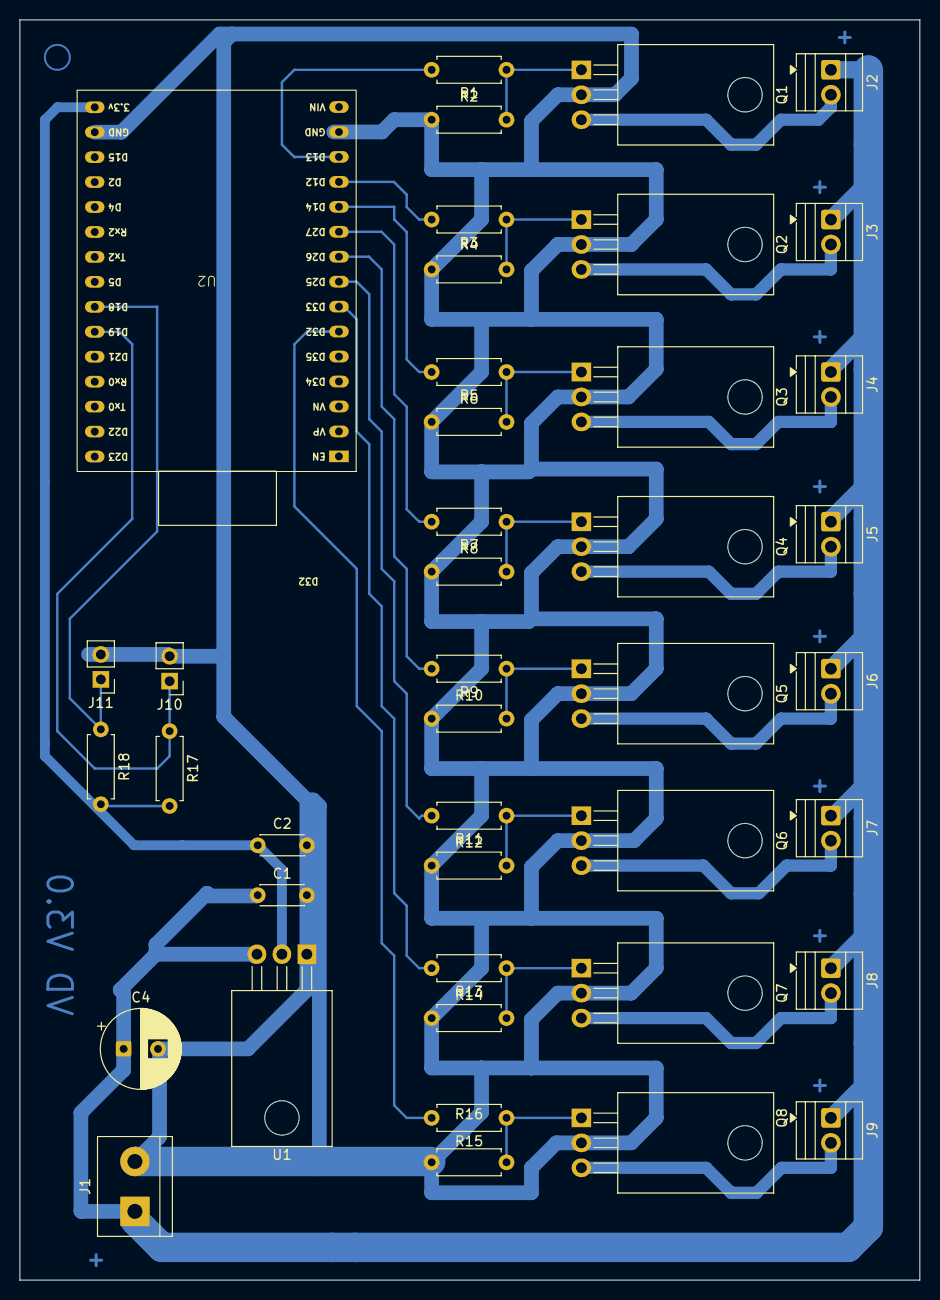
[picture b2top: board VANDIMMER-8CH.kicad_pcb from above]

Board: 2 copper layers, 91.6 x 128.3 mm, 42 parts (0 on the bottom side), 29 nets.

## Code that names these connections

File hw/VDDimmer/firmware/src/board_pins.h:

#pragma once
#include <Arduino.h>

#if ESP_ARDUINO_VERSION_MAJOR < 3
#error "Arduino-ESP32 3.x required (ledcAttach 3-arg API). See platformio.ini."
#endif

// =============================================================================
// VANDIMMER-4CH+2A  Rev A  --  ESP32-S3-WROOM-1U-N16 pin map
// =============================================================================
// Extracted from the exported netlist on 2026-09-04, NOT from any design
// document. The spec's section 7 pin table is the ORIGINAL plan and is wrong --
// the GPIO map changed twice during layout. Re-derive before trusting:
//
//   kicad-cli sch export netlist --format kicadsexpr \
//       -o vd.net hw/VDDimmer/VANDIMMER-4CH2A.kicad_sch
//
// then read U1's nodes. Board as ordered = git tag `ordered-revA` (37c12ab).
//
//   GPIO  Pad  Net           Function
//   IO3   15   GATE_IN1      PWM channel 1
//   IO9   17   GATE_IN2      PWM channel 2
//   IO11  19   GATE_IN3      PWM channel 3
//   IO13  21   GATE_IN4      PWM channel 4
//   IO21  23   ADDR1_DIN     addressable strip 1 data
//   IO47  24   ADDR2_DIN     addressable strip 2 data
//   IO48  25   ADDR_CLK      shared APA102 clock -- UNUSABLE, see below
//   IO45  26   STATUS_DIN    on-board WS2812B status LED (D7)
//   IO40  33   BTN1          J11, active low
//   IO39  32   BTN2          J12, active low
//   IO10  18   I2C_SCL       expansion header J13
//   IO12  20   I2C_SDA       expansion header J13
//   IO42  35   UART1_TX      J14
//   IO41  34   UART1_RX      J14
//   IO1   39   VIN_SENSE     ADC, 100k/10k divider off VIN_PROT
//   IO2   38   NTC_SENSE     ADC, 10k pull-up to +3V3 over 10k B3950 NTC
//   IO0   27   BOOT_IO0      strapping, broken out on J13.6
//   EN     3   EN_MCU        reset, broken out on J13.5
// =============================================================================

// --- PWM channels ------------------------------------------------------------
// LOW-SIDE N-FETs (20N06) behind U4, a 74HCT125 running from +5V.
// GPIO HIGH => buffer output HIGH => gate driven => channel ON.
//
// SAFETY: U4's four /OE pins (1, 4, 10, 13) are all tied to GND, so the buffer
// is permanently enabled. GATE_IN1..4 have no pulldown -- R5..R8 (10k) sit on
// the gate side and cannot fight a push-pull buffer output. While the ESP32 is
// in reset these four pins float, so a channel can glitch ON for the duration
// of the ROM boot window. pwm_preinit() must therefore be the FIRST thing
// setup() calls, and it latches the pads with gpio_hold_en() so the glitch
// cannot recur on a soft reset. A brief flash at COLD power-on is expected and
// is not a fault.
static constexpr uint8_t PWM_CHANNELS = 4;
static constexpr uint8_t PIN_GATE[PWM_CHANNELS] = { 3, 9, 11, 13 };

// --- Addressable outputs -----------------------------------------------------
// Data is level-shifted to 5 V by U5 (74HCT125) through 47R series resistors.
static constexpr uint8_t PIN_ADDR1_DIN  = 21;
static constexpr uint8_t PIN_ADDR2_DIN  = 47;
static constexpr uint8_t PIN_STATUS_DIN = 45;   // D7, on-board status pixel

// ADDR_CLK is a provision only and is deliberately never configured.
// R11/R12 (47R) are DNP, so U5.8 reaches neither J7.3 nor J8.3 -- the outputs
// are WS2812-style single-wire (data only). Note also that R11 and R12 are both
// fed from the SAME buffer output, so even fully fitted this is ONE clock
// shared by both strips, not two independent ones: two APA102 strips would have
// to be clocked in lockstep.
static constexpr uint8_t PIN_ADDR_CLK = 48;     // do not drive

// --- Buttons -----------------------------------------------------------------
// R43/R44 are external 10k pull-ups to +3V3; J11.2/J12.2 go to GND.
// Use INPUT, not INPUT_PULLUP.
static constexpr uint8_t PIN_BTN1 = 40;
static constexpr uint8_t PIN_BTN2 = 39;

// --- Analogue sense ----------------------------------------------------------
static constexpr uint8_t PIN_VIN_SENSE = 1;     // ADC1_CH0
static constexpr uint8_t PIN_NTC_SENSE = 2;     // ADC1_CH1

// R27 100k (VIN_PROT -> VIN_SENSE) / R28 10k (VIN_SENSE -> GND) => divide by 11
static constexpr float VIN_DIVIDER_RATIO = 11.0f;

// R29 10k 1% pull-up to +3V3, RT1 10k B3950 NTC to GND.
// The divider is ratiometric to the 3V3 rail while the ADC reference is
// internal, so rail error shows up directly as temperature error.
static constexpr float NTC_SERIES_OHMS  = 10000.0f;
static constexpr float NTC_NOMINAL_OHMS = 10000.0f;
static constexpr float NTC_NOMINAL_K    = 298.15f;   // 25 C
static constexpr float NTC_BETA         = 3950.0f;
static constexpr float NTC_RAIL_MV      = 3300.0f;

// --- Expansion (not driven by this firmware) ---------------------------------
static constexpr uint8_t PIN_I2C_SCL  = 10;
static constexpr uint8_t PIN_I2C_SDA  = 12;
static constexpr uint8_t PIN_UART1_TX = 42;
static constexpr uint8_t PIN_UART1_RX = 41;

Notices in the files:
README.md:
License: MIT
